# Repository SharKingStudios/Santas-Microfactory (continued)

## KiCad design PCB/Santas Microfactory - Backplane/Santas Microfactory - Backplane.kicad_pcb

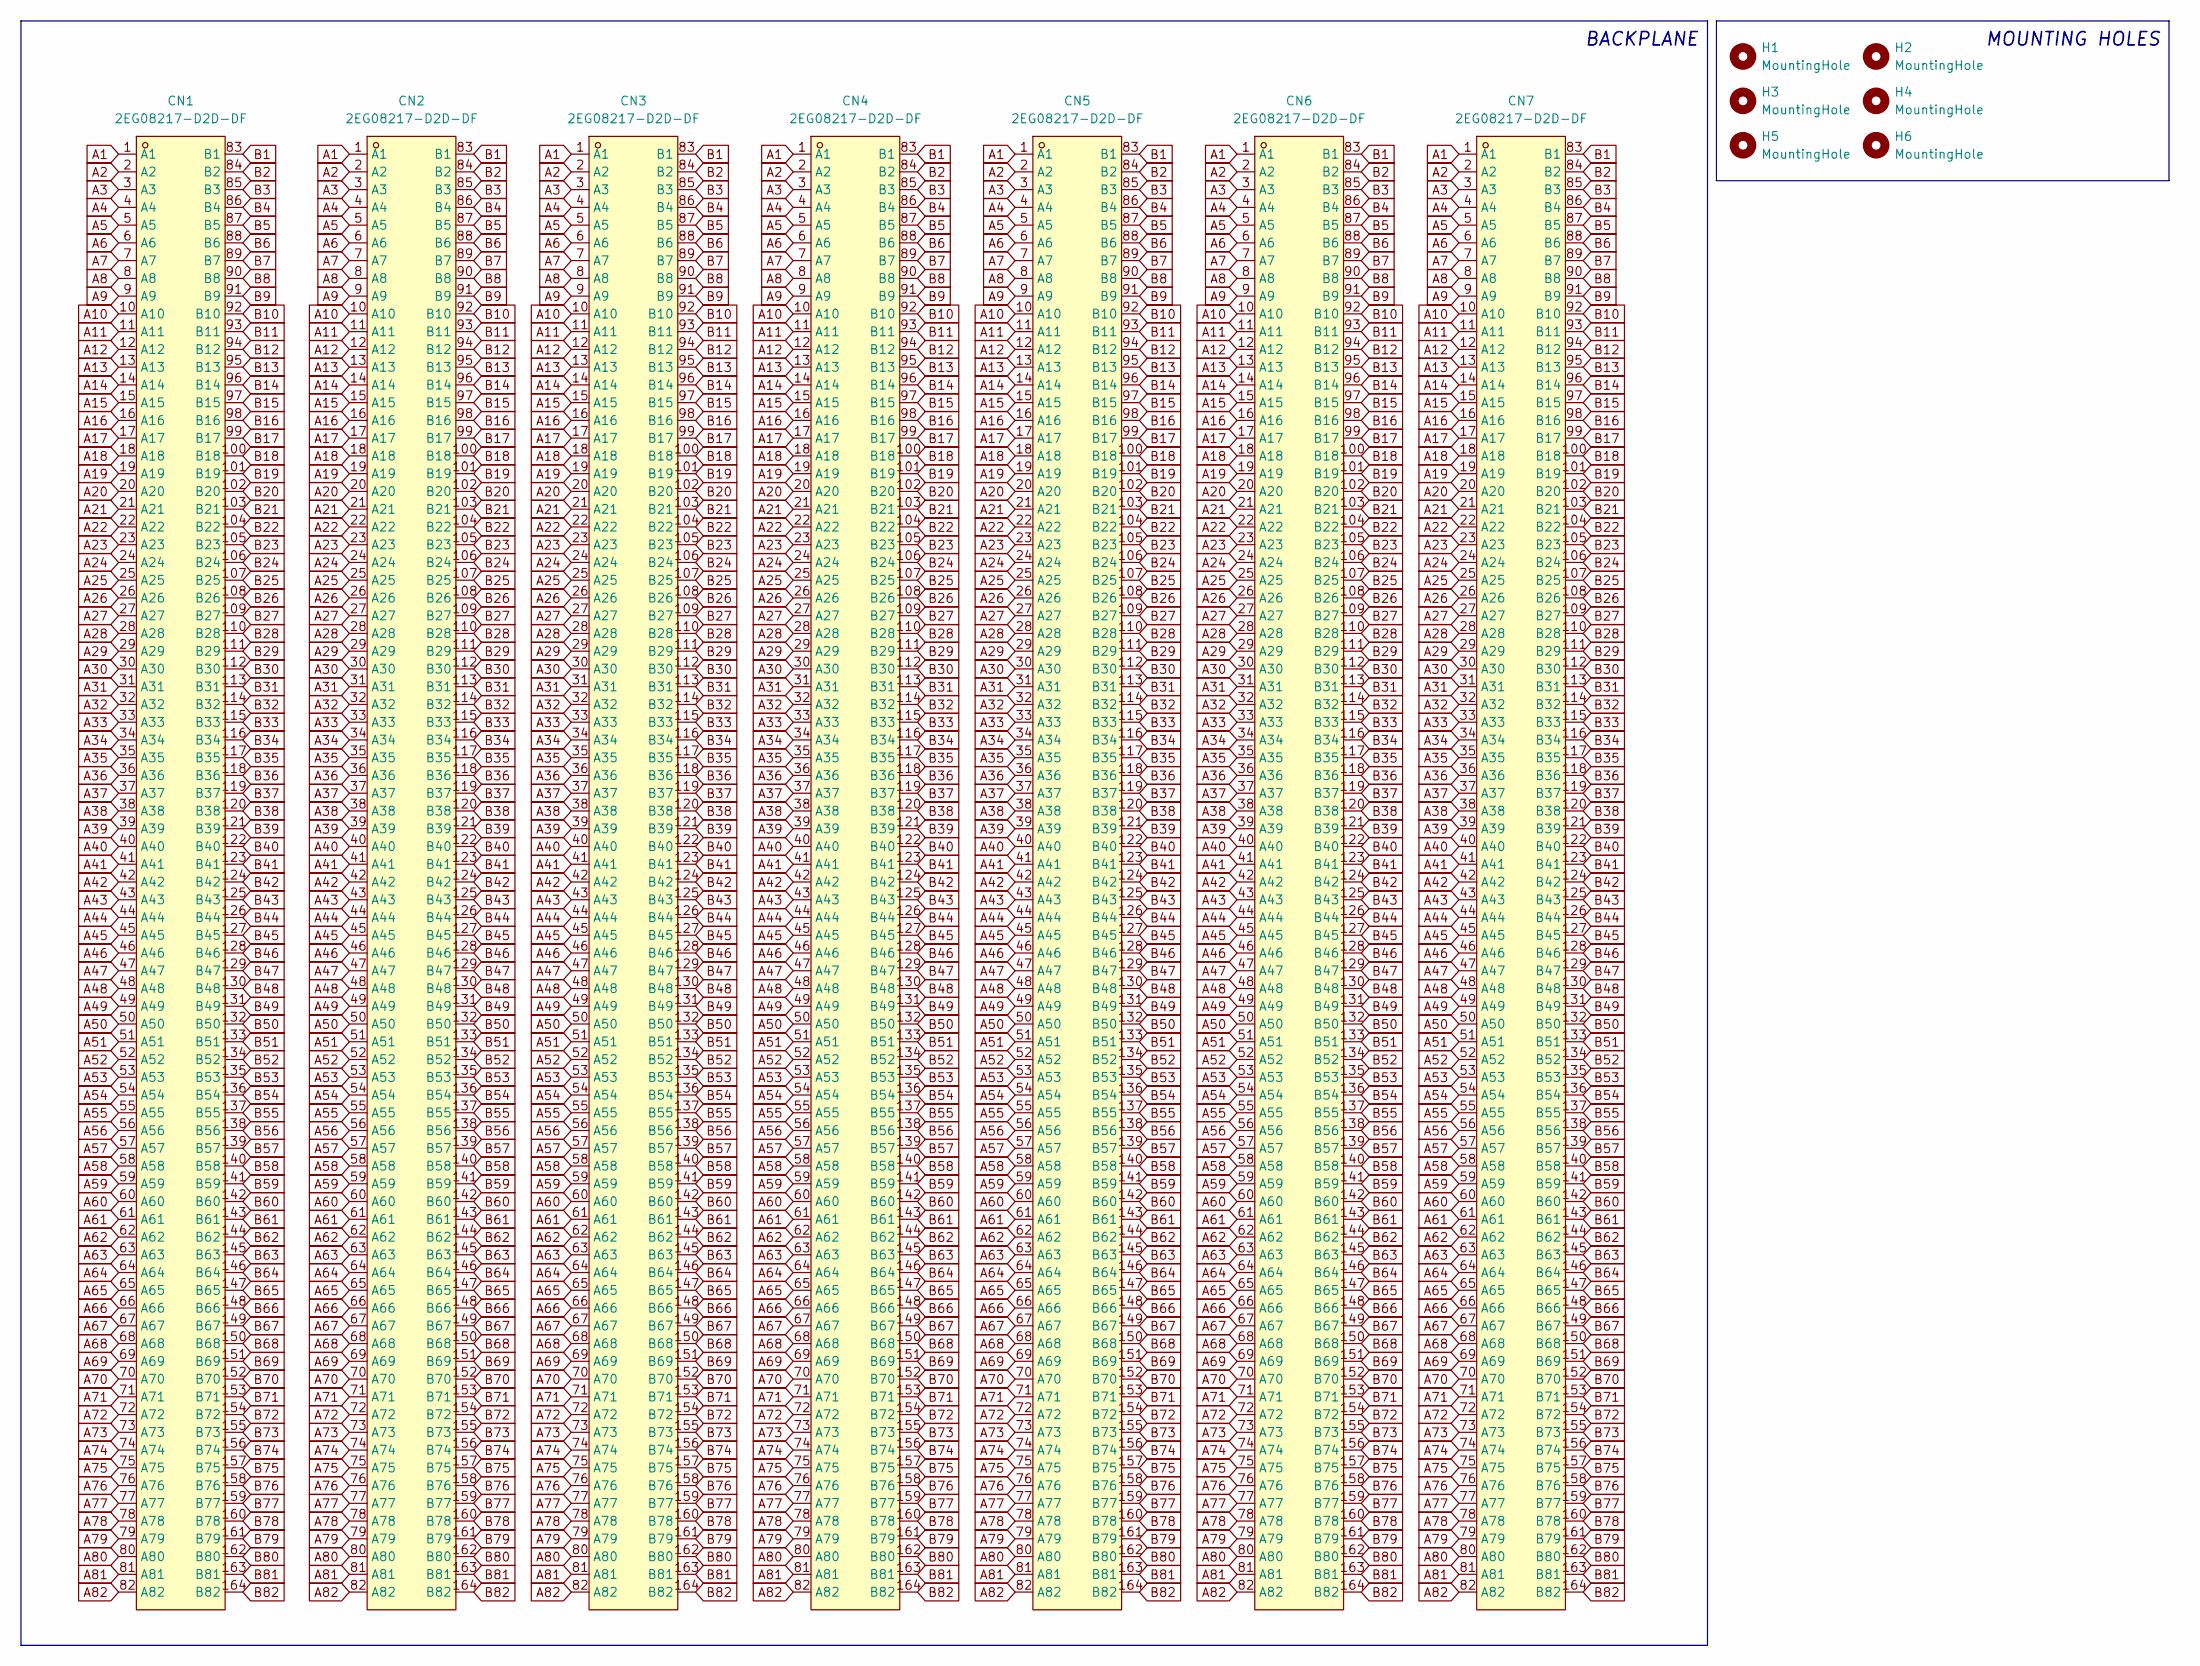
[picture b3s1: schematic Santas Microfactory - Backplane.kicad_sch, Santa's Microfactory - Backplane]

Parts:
CN1, CN2, CN3, CN4, CN5, CN6, CN7: 2EG08217-D2D-DF; CONN-TH_2EG08217-D2D-DF; LCSC Part C426228
H1, H2, H3, H4, H5, H6: MountingHole; MountingHole_3.2mm_M3_Pad_Via

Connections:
A1: CN1.1 (A1), CN2.1 (A1), CN3.1 (A1), CN4.1 (A1), CN5.1 (A1), CN6.1 (A1), CN7.1 (A1)
A2: CN1.2 (A2), CN2.2 (A2), CN3.2 (A2), CN4.2 (A2), CN5.2 (A2), CN6.2 (A2), CN7.2 (A2)
A3: CN1.3 (A3), CN2.3 (A3), CN3.3 (A3), CN4.3 (A3), CN5.3 (A3), CN6.3 (A3), CN7.3 (A3)
A4: CN1.4 (A4), CN2.4 (A4), CN3.4 (A4), CN4.4 (A4), CN5.4 (A4), CN6.4 (A4), CN7.4 (A4)
A5: CN1.5 (A5), CN2.5 (A5), CN3.5 (A5), CN4.5 (A5), CN5.5 (A5), CN6.5 (A5), CN7.5 (A5)
A6: CN1.6 (A6), CN2.6 (A6), CN3.6 (A6), CN4.6 (A6), CN5.6 (A6), CN6.6 (A6), CN7.6 (A6)
A7: CN1.7 (A7), CN2.7 (A7), CN3.7 (A7), CN4.7 (A7), CN5.7 (A7), CN6.7 (A7), CN7.7 (A7)
A8: CN1.8 (A8), CN2.8 (A8), CN3.8 (A8), CN4.8 (A8), CN5.8 (A8), CN6.8 (A8), CN7.8 (A8)
A9: CN1.9 (A9), CN2.9 (A9), CN3.9 (A9), CN4.9 (A9), CN5.9 (A9), CN6.9 (A9), CN7.9 (A9)
A10: CN1.10 (A10), CN2.10 (A10), CN3.10 (A10), CN4.10 (A10), CN5.10 (A10), CN6.10 (A10), CN7.10 (A10)
A11: CN1.11 (A11), CN2.11 (A11), CN3.11 (A11), CN4.11 (A11), CN5.11 (A11), CN6.11 (A11), CN7.11 (A11)
A12: CN1.12 (A12), CN2.12 (A12), CN3.12 (A12), CN4.12 (A12), CN5.12 (A12), CN6.12 (A12), CN7.12 (A12)
A13: CN1.13 (A13), CN2.13 (A13), CN3.13 (A13), CN4.13 (A13), CN5.13 (A13), CN6.13 (A13), CN7.13 (A13)
A14: CN1.14 (A14), CN2.14 (A14), CN3.14 (A14), CN4.14 (A14), CN5.14 (A14), CN6.14 (A14), CN7.14 (A14)
A15: CN1.15 (A15), CN2.15 (A15), CN3.15 (A15), CN4.15 (A15), CN5.15 (A15), CN6.15 (A15), CN7.15 (A15)
A16: CN1.16 (A16), CN2.16 (A16), CN3.16 (A16), CN4.16 (A16), CN5.16 (A16), CN6.16 (A16), CN7.16 (A16)
A17: CN1.17 (A17), CN2.17 (A17), CN3.17 (A17), CN4.17 (A17), CN5.17 (A17), CN6.17 (A17), CN7.17 (A17)
A18: CN1.18 (A18), CN2.18 (A18), CN3.18 (A18), CN4.18 (A18), CN5.18 (A18), CN6.18 (A18), CN7.18 (A18)
A19: CN1.19 (A19), CN2.19 (A19), CN3.19 (A19), CN4.19 (A19), CN5.19 (A19), CN6.19 (A19), CN7.19 (A19)
A20: CN1.20 (A20), CN2.20 (A20), CN3.20 (A20), CN4.20 (A20), CN5.20 (A20), CN6.20 (A20), CN7.20 (A20)
A21: CN1.21 (A21), CN2.21 (A21), CN3.21 (A21), CN4.21 (A21), CN5.21 (A21), CN6.21 (A21), CN7.21 (A21)
A22: CN1.22 (A22), CN2.22 (A22), CN3.22 (A22), CN4.22 (A22), CN5.22 (A22), CN6.22 (A22), CN7.22 (A22)
A23: CN1.23 (A23), CN2.23 (A23), CN3.23 (A23), CN4.23 (A23), CN5.23 (A23), CN6.23 (A23), CN7.23 (A23)
A24: CN1.24 (A24), CN2.24 (A24), CN3.24 (A24), CN4.24 (A24), CN5.24 (A24), CN6.24 (A24), CN7.24 (A24)
A25: CN1.25 (A25), CN2.25 (A25), CN3.25 (A25), CN4.25 (A25), CN5.25 (A25), CN6.25 (A25), CN7.25 (A25)
A26: CN1.26 (A26), CN2.26 (A26), CN3.26 (A26), CN4.26 (A26), CN5.26 (A26), CN6.26 (A26), CN7.26 (A26)
A27: CN1.27 (A27), CN2.27 (A27), CN3.27 (A27), CN4.27 (A27), CN5.27 (A27), CN6.27 (A27), CN7.27 (A27)
A28: CN1.28 (A28), CN2.28 (A28), CN3.28 (A28), CN4.28 (A28), CN5.28 (A28), CN6.28 (A28), CN7.28 (A28)
A29: CN1.29 (A29), CN2.29 (A29), CN3.29 (A29), CN4.29 (A29), CN5.29 (A29), CN6.29 (A29), CN7.29 (A29)
A30: CN1.30 (A30), CN2.30 (A30), CN3.30 (A30), CN4.30 (A30), CN5.30 (A30), CN6.30 (A30), CN7.30 (A30)
A31: CN1.31 (A31), CN2.31 (A31), CN3.31 (A31), CN4.31 (A31), CN5.31 (A31), CN6.31 (A31), CN7.31 (A31)
A32: CN1.32 (A32), CN2.32 (A32), CN3.32 (A32), CN4.32 (A32), CN5.32 (A32), CN6.32 (A32), CN7.32 (A32)
A33: CN1.33 (A33), CN2.33 (A33), CN3.33 (A33), CN4.33 (A33), CN5.33 (A33), CN6.33 (A33), CN7.33 (A33)
A34: CN1.34 (A34), CN2.34 (A34), CN3.34 (A34), CN4.34 (A34), CN5.34 (A34), CN6.34 (A34), CN7.34 (A34)
A35: CN1.35 (A35), CN2.35 (A35), CN3.35 (A35), CN4.35 (A35), CN5.35 (A35), CN6.35 (A35), CN7.35 (A35)
A36: CN1.36 (A36), CN2.36 (A36), CN3.36 (A36), CN4.36 (A36), CN5.36 (A36), CN6.36 (A36), CN7.36 (A36)
A37: CN1.37 (A37), CN2.37 (A37), CN3.37 (A37), CN4.37 (A37), CN5.37 (A37), CN6.37 (A37), CN7.37 (A37)
A38: CN1.38 (A38), CN2.38 (A38), CN3.38 (A38), CN4.38 (A38), CN5.38 (A38), CN6.38 (A38), CN7.38 (A38)
A39: CN1.39 (A39), CN2.39 (A39), CN3.39 (A39), CN4.39 (A39), CN5.39 (A39), CN6.39 (A39), CN7.39 (A39)
A40: CN1.40 (A40), CN2.40 (A40), CN3.40 (A40), CN4.40 (A40), CN5.40 (A40), CN6.40 (A40), CN7.40 (A40)
A41: CN1.41 (A41), CN2.41 (A41), CN3.41 (A41), CN4.41 (A41), CN5.41 (A41), CN6.41 (A41), CN7.41 (A41)
A42: CN1.42 (A42), CN2.42 (A42), CN3.42 (A42), CN4.42 (A42), CN5.42 (A42), CN6.42 (A42), CN7.42 (A42)
A43: CN1.43 (A43), CN2.43 (A43), CN3.43 (A43), CN4.43 (A43), CN5.43 (A43), CN6.43 (A43), CN7.43 (A43)
A44: CN1.44 (A44), CN2.44 (A44), CN3.44 (A44), CN4.44 (A44), CN5.44 (A44), CN6.44 (A44), CN7.44 (A44)
A45: CN1.45 (A45), CN2.45 (A45), CN3.45 (A45), CN4.45 (A45), CN5.45 (A45), CN6.45 (A45), CN7.45 (A45)
A46: CN1.46 (A46), CN2.46 (A46), CN3.46 (A46), CN4.46 (A46), CN5.46 (A46), CN6.46 (A46), CN7.46 (A46)
A47: CN1.47 (A47), CN2.47 (A47), CN3.47 (A47), CN4.47 (A47), CN5.47 (A47), CN6.47 (A47), CN7.47 (A47)
A48: CN1.48 (A48), CN2.48 (A48), CN3.48 (A48), CN4.48 (A48), CN5.48 (A48), CN6.48 (A48), CN7.48 (A48)
A49: CN1.49 (A49), CN2.49 (A49), CN3.49 (A49), CN4.49 (A49), CN5.49 (A49), CN6.49 (A49), CN7.49 (A49)
A50: CN1.50 (A50), CN2.50 (A50), CN3.50 (A50), CN4.50 (A50), CN5.50 (A50), CN6.50 (A50), CN7.50 (A50)
A51: CN1.51 (A51), CN2.51 (A51), CN3.51 (A51), CN4.51 (A51), CN5.51 (A51), CN6.51 (A51), CN7.51 (A51)
A52: CN1.52 (A52), CN2.52 (A52), CN3.52 (A52), CN4.52 (A52), CN5.52 (A52), CN6.52 (A52), CN7.52 (A52)
A53: CN1.53 (A53), CN2.53 (A53), CN3.53 (A53), CN4.53 (A53), CN5.53 (A53), CN6.53 (A53), CN7.53 (A53)
A54: CN1.54 (A54), CN2.54 (A54), CN3.54 (A54), CN4.54 (A54), CN5.54 (A54), CN6.54 (A54), CN7.54 (A54)
A55: CN1.55 (A55), CN2.55 (A55), CN3.55 (A55), CN4.55 (A55), CN5.55 (A55), CN6.55 (A55), CN7.55 (A55)
A56: CN1.56 (A56), CN2.56 (A56), CN3.56 (A56), CN4.56 (A56), CN5.56 (A56), CN6.56 (A56), CN7.56 (A56)
A57: CN1.57 (A57), CN2.57 (A57), CN3.57 (A57), CN4.57 (A57), CN5.57 (A57), CN6.57 (A57), CN7.57 (A57)
A58: CN1.58 (A58), CN2.58 (A58), CN3.58 (A58), CN4.58 (A58), CN5.58 (A58), CN6.58 (A58), CN7.58 (A58)
A59: CN1.59 (A59), CN2.59 (A59), CN3.59 (A59), CN4.59 (A59), CN5.59 (A59), CN6.59 (A59), CN7.59 (A59)
A60: CN1.60 (A60), CN2.60 (A60), CN3.60 (A60), CN4.60 (A60), CN5.60 (A60), CN6.60 (A60), CN7.60 (A60)
A61: CN1.61 (A61), CN2.61 (A61), CN3.61 (A61), CN4.61 (A61), CN5.61 (A61), CN6.61 (A61), CN7.61 (A61)
A62: CN1.62 (A62), CN2.62 (A62), CN3.62 (A62), CN4.62 (A62), CN5.62 (A62), CN6.62 (A62), CN7.62 (A62)
A63: CN1.63 (A63), CN2.63 (A63), CN3.63 (A63), CN4.63 (A63), CN5.63 (A63), CN6.63 (A63), CN7.63 (A63)
A64: CN1.64 (A64), CN2.64 (A64), CN3.64 (A64), CN4.64 (A64), CN5.64 (A64), CN6.64 (A64), CN7.64 (A64)
A65: CN1.65 (A65), CN2.65 (A65), CN3.65 (A65), CN4.65 (A65), CN5.65 (A65), CN6.65 (A65), CN7.65 (A65)
A66: CN1.66 (A66), CN2.66 (A66), CN3.66 (A66), CN4.66 (A66), CN5.66 (A66), CN6.66 (A66), CN7.66 (A66)
A67: CN1.67 (A67), CN2.67 (A67), CN3.67 (A67), CN4.67 (A67), CN5.67 (A67), CN6.67 (A67), CN7.67 (A67)
A68: CN1.68 (A68), CN2.68 (A68), CN3.68 (A68), CN4.68 (A68), CN5.68 (A68), CN6.68 (A68), CN7.68 (A68)
A69: CN1.69 (A69), CN2.69 (A69), CN3.69 (A69), CN4.69 (A69), CN5.69 (A69), CN6.69 (A69), CN7.69 (A69)
A70: CN1.70 (A70), CN2.70 (A70), CN3.70 (A70), CN4.70 (A70), CN5.70 (A70), CN6.70 (A70), CN7.70 (A70)
A71: CN1.71 (A71), CN2.71 (A71), CN3.71 (A71), CN4.71 (A71), CN5.71 (A71), CN6.71 (A71), CN7.71 (A71)
A72: CN1.72 (A72), CN2.72 (A72), CN3.72 (A72), CN4.72 (A72), CN5.72 (A72), CN6.72 (A72), CN7.72 (A72)
A73: CN1.73 (A73), CN2.73 (A73), CN3.73 (A73), CN4.73 (A73), CN5.73 (A73), CN6.73 (A73), CN7.73 (A73)
A74: CN1.74 (A74), CN2.74 (A74), CN3.74 (A74), CN4.74 (A74), CN5.74 (A74), CN6.74 (A74), CN7.74 (A74)
A75: CN1.75 (A75), CN2.75 (A75), CN3.75 (A75), CN4.75 (A75), CN5.75 (A75), CN6.75 (A75), CN7.75 (A75)
A76: CN1.76 (A76), CN2.76 (A76), CN3.76 (A76), CN4.76 (A76), CN5.76 (A76), CN6.76 (A76), CN7.76 (A76)
A77: CN1.77 (A77), CN2.77 (A77), CN3.77 (A77), CN4.77 (A77), CN5.77 (A77), CN6.77 (A77), CN7.77 (A77)
A78: CN1.78 (A78), CN2.78 (A78), CN3.78 (A78), CN4.78 (A78), CN5.78 (A78), CN6.78 (A78), CN7.78 (A78)
A79: CN1.79 (A79), CN2.79 (A79), CN3.79 (A79), CN4.79 (A79), CN5.79 (A79), CN6.79 (A79), CN7.79 (A79)
A80: CN1.80 (A80), CN2.80 (A80), CN3.80 (A80), CN4.80 (A80), CN5.80 (A80), CN6.80 (A80), CN7.80 (A80)
A81: CN1.81 (A81), CN2.81 (A81), CN3.81 (A81), CN4.81 (A81), CN5.81 (A81), CN6.81 (A81), CN7.81 (A81)
A82: CN1.82 (A82), CN2.82 (A82), CN3.82 (A82), CN4.82 (A82), CN5.82 (A82), CN6.82 (A82), CN7.82 (A82)
B1: CN1.83 (B1), CN2.83 (B1), CN3.83 (B1), CN4.83 (B1), CN5.83 (B1), CN6.83 (B1), CN7.83 (B1)
B2: CN1.84 (B2), CN2.84 (B2), CN3.84 (B2), CN4.84 (B2), CN5.84 (B2), CN6.84 (B2), CN7.84 (B2)
B3: CN1.85 (B3), CN2.85 (B3), CN3.85 (B3), CN4.85 (B3), CN5.85 (B3), CN6.85 (B3), CN7.85 (B3)
B4: CN1.86 (B4), CN2.86 (B4), CN3.86 (B4), CN4.86 (B4), CN5.86 (B4), CN6.86 (B4), CN7.86 (B4)
B5: CN1.87 (B5), CN2.87 (B5), CN3.87 (B5), CN4.87 (B5), CN5.87 (B5), CN6.87 (B5), CN7.87 (B5)
B6: CN1.88 (B6), CN2.88 (B6), CN3.88 (B6), CN4.88 (B6), CN5.88 (B6), CN6.88 (B6), CN7.88 (B6)
B7: CN1.89 (B7), CN2.89 (B7), CN3.89 (B7), CN4.89 (B7), CN5.89 (B7), CN6.89 (B7), CN7.89 (B7)
B8: CN1.90 (B8), CN2.90 (B8), CN3.90 (B8), CN4.90 (B8), CN5.90 (B8), CN6.90 (B8), CN7.90 (B8)
B9: CN1.91 (B9), CN2.91 (B9), CN3.91 (B9), CN4.91 (B9), CN5.91 (B9), CN6.91 (B9), CN7.91 (B9)
B10: CN1.92 (B10), CN2.92 (B10), CN3.92 (B10), CN4.92 (B10), CN5.92 (B10), CN6.92 (B10), CN7.92 (B10)
B11: CN1.93 (B11), CN2.93 (B11), CN3.93 (B11), CN4.93 (B11), CN5.93 (B11), CN6.93 (B11), CN7.93 (B11)
B12: CN1.94 (B12), CN2.94 (B12), CN3.94 (B12), CN4.94 (B12), CN5.94 (B12), CN6.94 (B12), CN7.94 (B12)
B13: CN1.95 (B13), CN2.95 (B13), CN3.95 (B13), CN4.95 (B13), CN5.95 (B13), CN6.95 (B13), CN7.95 (B13)
B14: CN1.96 (B14), CN2.96 (B14), CN3.96 (B14), CN4.96 (B14), CN5.96 (B14), CN6.96 (B14), CN7.96 (B14)
B15: CN1.97 (B15), CN2.97 (B15), CN3.97 (B15), CN4.97 (B15), CN5.97 (B15), CN6.97 (B15), CN7.97 (B15)
B16: CN1.98 (B16), CN2.98 (B16), CN3.98 (B16), CN4.98 (B16), CN5.98 (B16), CN6.98 (B16), CN7.98 (B16)
B17: CN1.99 (B17), CN2.99 (B17), CN3.99 (B17), CN4.99 (B17), CN5.99 (B17), CN6.99 (B17), CN7.99 (B17)
B18: CN1.100 (B18), CN2.100 (B18), CN3.100 (B18), CN4.100 (B18), CN5.100 (B18), CN6.100 (B18), CN7.100 (B18)
B19: CN1.101 (B19), CN2.101 (B19), CN3.101 (B19), CN4.101 (B19), CN5.101 (B19), CN6.101 (B19), CN7.101 (B19)
B20: CN1.102 (B20), CN2.102 (B20), CN3.102 (B20), CN4.102 (B20), CN5.102 (B20), CN6.102 (B20), CN7.102 (B20)
B21: CN1.103 (B21), CN2.103 (B21), CN3.103 (B21), CN4.103 (B21), CN5.103 (B21), CN6.103 (B21), CN7.103 (B21)
B22: CN1.104 (B22), CN2.104 (B22), CN3.104 (B22), CN4.104 (B22), CN5.104 (B22), CN6.104 (B22), CN7.104 (B22)
B23: CN1.105 (B23), CN2.105 (B23), CN3.105 (B23), CN4.105 (B23), CN5.105 (B23), CN6.105 (B23), CN7.105 (B23)
B24: CN1.106 (B24), CN2.106 (B24), CN3.106 (B24), CN4.106 (B24), CN5.106 (B24), CN6.106 (B24), CN7.106 (B24)
B25: CN1.107 (B25), CN2.107 (B25), CN3.107 (B25), CN4.107 (B25), CN5.107 (B25), CN6.107 (B25), CN7.107 (B25)
B26: CN1.108 (B26), CN2.108 (B26), CN3.108 (B26), CN4.108 (B26), CN5.108 (B26), CN6.108 (B26), CN7.108 (B26)
B27: CN1.109 (B27), CN2.109 (B27), CN3.109 (B27), CN4.109 (B27), CN5.109 (B27), CN6.109 (B27), CN7.109 (B27)
B28: CN1.110 (B28), CN2.110 (B28), CN3.110 (B28), CN4.110 (B28), CN5.110 (B28), CN6.110 (B28), CN7.110 (B28)
B29: CN1.111 (B29), CN2.111 (B29), CN3.111 (B29), CN4.111 (B29), CN5.111 (B29), CN6.111 (B29), CN7.111 (B29)
B30: CN1.112 (B30), CN2.112 (B30), CN3.112 (B30), CN4.112 (B30), CN5.112 (B30), CN6.112 (B30), CN7.112 (B30)
B31: CN1.113 (B31), CN2.113 (B31), CN3.113 (B31), CN4.113 (B31), CN5.113 (B31), CN6.113 (B31), CN7.113 (B31)
B32: CN1.114 (B32), CN2.114 (B32), CN3.114 (B32), CN4.114 (B32), CN5.114 (B32), CN6.114 (B32), CN7.114 (B32)
B33: CN1.115 (B33), CN2.115 (B33), CN3.115 (B33), CN4.115 (B33), CN5.115 (B33), CN6.115 (B33), CN7.115 (B33)
B34: CN1.116 (B34), CN2.116 (B34), CN3.116 (B34), CN4.116 (B34), CN5.116 (B34), CN6.116 (B34), CN7.116 (B34)
B35: CN1.117 (B35), CN2.117 (B35), CN3.117 (B35), CN4.117 (B35), CN5.117 (B35), CN6.117 (B35), CN7.117 (B35)
B36: CN1.118 (B36), CN2.118 (B36), CN3.118 (B36), CN4.118 (B36), CN5.118 (B36), CN6.118 (B36), CN7.118 (B36)
B37: CN1.119 (B37), CN2.119 (B37), CN3.119 (B37), CN4.119 (B37), CN5.119 (B37), CN6.119 (B37), CN7.119 (B37)
B38: CN1.120 (B38), CN2.120 (B38), CN3.120 (B38), CN4.120 (B38), CN5.120 (B38), CN6.120 (B38), CN7.120 (B38)
B39: CN1.121 (B39), CN2.121 (B39), CN3.121 (B39), CN4.121 (B39), CN5.121 (B39), CN6.121 (B39), CN7.121 (B39)
B40: CN1.122 (B40), CN2.122 (B40), CN3.122 (B40), CN4.122 (B40), CN5.122 (B40), CN6.122 (B40), CN7.122 (B40)
B41: CN1.123 (B41), CN2.123 (B41), CN3.123 (B41), CN4.123 (B41), CN5.123 (B41), CN6.123 (B41), CN7.123 (B41)
B42: CN1.124 (B42), CN2.124 (B42), CN3.124 (B42), CN4.124 (B42), CN5.124 (B42), CN6.124 (B42), CN7.124 (B42)
B43: CN1.125 (B43), CN2.125 (B43), CN3.125 (B43), CN4.125 (B43), CN5.125 (B43), CN6.125 (B43), CN7.125 (B43)
B44: CN1.126 (B44), CN2.126 (B44), CN3.126 (B44), CN4.126 (B44), CN5.126 (B44), CN6.126 (B44), CN7.126 (B44)
B45: CN1.127 (B45), CN2.127 (B45), CN3.127 (B45), CN4.127 (B45), CN5.127 (B45), CN6.127 (B45), CN7.127 (B45)
B46: CN1.128 (B46), CN2.128 (B46), CN3.128 (B46), CN4.128 (B46), CN5.128 (B46), CN6.128 (B46), CN7.128 (B46)
B47: CN1.129 (B47), CN2.129 (B47), CN3.129 (B47), CN4.129 (B47), CN5.129 (B47), CN6.129 (B47), CN7.129 (B47)
B48: CN1.130 (B48), CN2.130 (B48), CN3.130 (B48), CN4.130 (B48), CN5.130 (B48), CN6.130 (B48), CN7.130 (B48)
B49: CN1.131 (B49), CN2.131 (B49), CN3.131 (B49), CN4.131 (B49), CN5.131 (B49), CN6.131 (B49), CN7.131 (B49)
B50: CN1.132 (B50), CN2.132 (B50), CN3.132 (B50), CN4.132 (B50), CN5.132 (B50), CN6.132 (B50), CN7.132 (B50)
B51: CN1.133 (B51), CN2.133 (B51), CN3.133 (B51), CN4.133 (B51), CN5.133 (B51), CN6.133 (B51), CN7.133 (B51)
B52: CN1.134 (B52), CN2.134 (B52), CN3.134 (B52), CN4.134 (B52), CN5.134 (B52), CN6.134 (B52), CN7.134 (B52)
B53: CN1.135 (B53), CN2.135 (B53), CN3.135 (B53), CN4.135 (B53), CN5.135 (B53), CN6.135 (B53), CN7.135 (B53)
B54: CN1.136 (B54), CN2.136 (B54), CN3.136 (B54), CN4.136 (B54), CN5.136 (B54), CN6.136 (B54), CN7.136 (B54)
B55: CN1.137 (B55), CN2.137 (B55), CN3.137 (B55), CN4.137 (B55), CN5.137 (B55), CN6.137 (B55), CN7.137 (B55)
B56: CN1.138 (B56), CN2.138 (B56), CN3.138 (B56), CN4.138 (B56), CN5.138 (B56), CN6.138 (B56), CN7.138 (B56)
B57: CN1.139 (B57), CN2.139 (B57), CN3.139 (B57), CN4.139 (B57), CN5.139 (B57), CN6.139 (B57), CN7.139 (B57)
B58: CN1.140 (B58), CN2.140 (B58), CN3.140 (B58), CN4.140 (B58), CN5.140 (B58), CN6.140 (B58), CN7.140 (B58)
B59: CN1.141 (B59), CN2.141 (B59), CN3.141 (B59), CN4.141 (B59), CN5.141 (B59), CN6.141 (B59), CN7.141 (B59)
B60: CN1.142 (B60), CN2.142 (B60), CN3.142 (B60), CN4.142 (B60), CN5.142 (B60), CN6.142 (B60), CN7.142 (B60)
B61: CN1.143 (B61), CN2.143 (B61), CN3.143 (B61), CN4.143 (B61), CN5.143 (B61), CN6.143 (B61), CN7.143 (B61)
B62: CN1.144 (B62), CN2.144 (B62), CN3.144 (B62), CN4.144 (B62), CN5.144 (B62), CN6.144 (B62), CN7.144 (B62)
B63: CN1.145 (B63), CN2.145 (B63), CN3.145 (B63), CN4.145 (B63), CN5.145 (B63), CN6.145 (B63), CN7.145 (B63)
B64: CN1.146 (B64), CN2.146 (B64), CN3.146 (B64), CN4.146 (B64), CN5.146 (B64), CN6.146 (B64), CN7.146 (B64)
B65: CN1.147 (B65), CN2.147 (B65), CN3.147 (B65), CN4.147 (B65), CN5.147 (B65), CN6.147 (B65), CN7.147 (B65)
B66: CN1.148 (B66), CN2.148 (B66), CN3.148 (B66), CN4.148 (B66), CN5.148 (B66), CN6.148 (B66), CN7.148 (B66)
B67: CN1.149 (B67), CN2.149 (B67), CN3.149 (B67), CN4.149 (B67), CN5.149 (B67), CN6.149 (B67), CN7.149 (B67)
B68: CN1.150 (B68), CN2.150 (B68), CN3.150 (B68), CN4.150 (B68), CN5.150 (B68), CN6.150 (B68), CN7.150 (B68)
B69: CN1.151 (B69), CN2.151 (B69), CN3.151 (B69), CN4.151 (B69), CN5.151 (B69), CN6.151 (B69), CN7.151 (B69)
B70: CN1.152 (B70), CN2.152 (B70), CN3.152 (B70), CN4.152 (B70), CN5.152 (B70), CN6.152 (B70), CN7.152 (B70)
B71: CN1.153 (B71), CN2.153 (B71), CN3.153 (B71), CN4.153 (B71), CN5.153 (B71), CN6.153 (B71), CN7.153 (B71)
B72: CN1.154 (B72), CN2.154 (B72), CN3.154 (B72), CN4.154 (B72), CN5.154 (B72), CN6.154 (B72), CN7.154 (B72)
B73: CN1.155 (B73), CN2.155 (B73), CN3.155 (B73), CN4.155 (B73), CN5.155 (B73), CN6.155 (B73), CN7.155 (B73)
B74: CN1.156 (B74), CN2.156 (B74), CN3.156 (B74), CN4.156 (B74), CN5.156 (B74), CN6.156 (B74), CN7.156 (B74)
B75: CN1.157 (B75), CN2.157 (B75), CN3.157 (B75), CN4.157 (B75), CN5.157 (B75), CN6.157 (B75), CN7.157 (B75)
B76: CN1.158 (B76), CN2.158 (B76), CN3.158 (B76), CN4.158 (B76), CN5.158 (B76), CN6.158 (B76), CN7.158 (B76)
B77: CN1.159 (B77), CN2.159 (B77), CN3.159 (B77), CN4.159 (B77), CN5.159 (B77), CN6.159 (B77), CN7.159 (B77)
B78: CN1.160 (B78), CN2.160 (B78), CN3.160 (B78), CN4.160 (B78), CN5.160 (B78), CN6.160 (B78), CN7.160 (B78)
B79: CN1.161 (B79), CN2.161 (B79), CN3.161 (B79), CN4.161 (B79), CN5.161 (B79), CN6.161 (B79), CN7.161 (B79)
B80: CN1.162 (B80), CN2.162 (B80), CN3.162 (B80), CN4.162 (B80), CN5.162 (B80), CN6.162 (B80), CN7.162 (B80)
B81: CN1.163 (B81), CN2.163 (B81), CN3.163 (B81), CN4.163 (B81), CN5.163 (B81), CN6.163 (B81), CN7.163 (B81)
B82: CN1.164 (B82), CN2.164 (B82), CN3.164 (B82), CN4.164 (B82), CN5.164 (B82), CN6.164 (B82), CN7.164 (B82)

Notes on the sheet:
MOUNTING HOLES
BACKPLANE

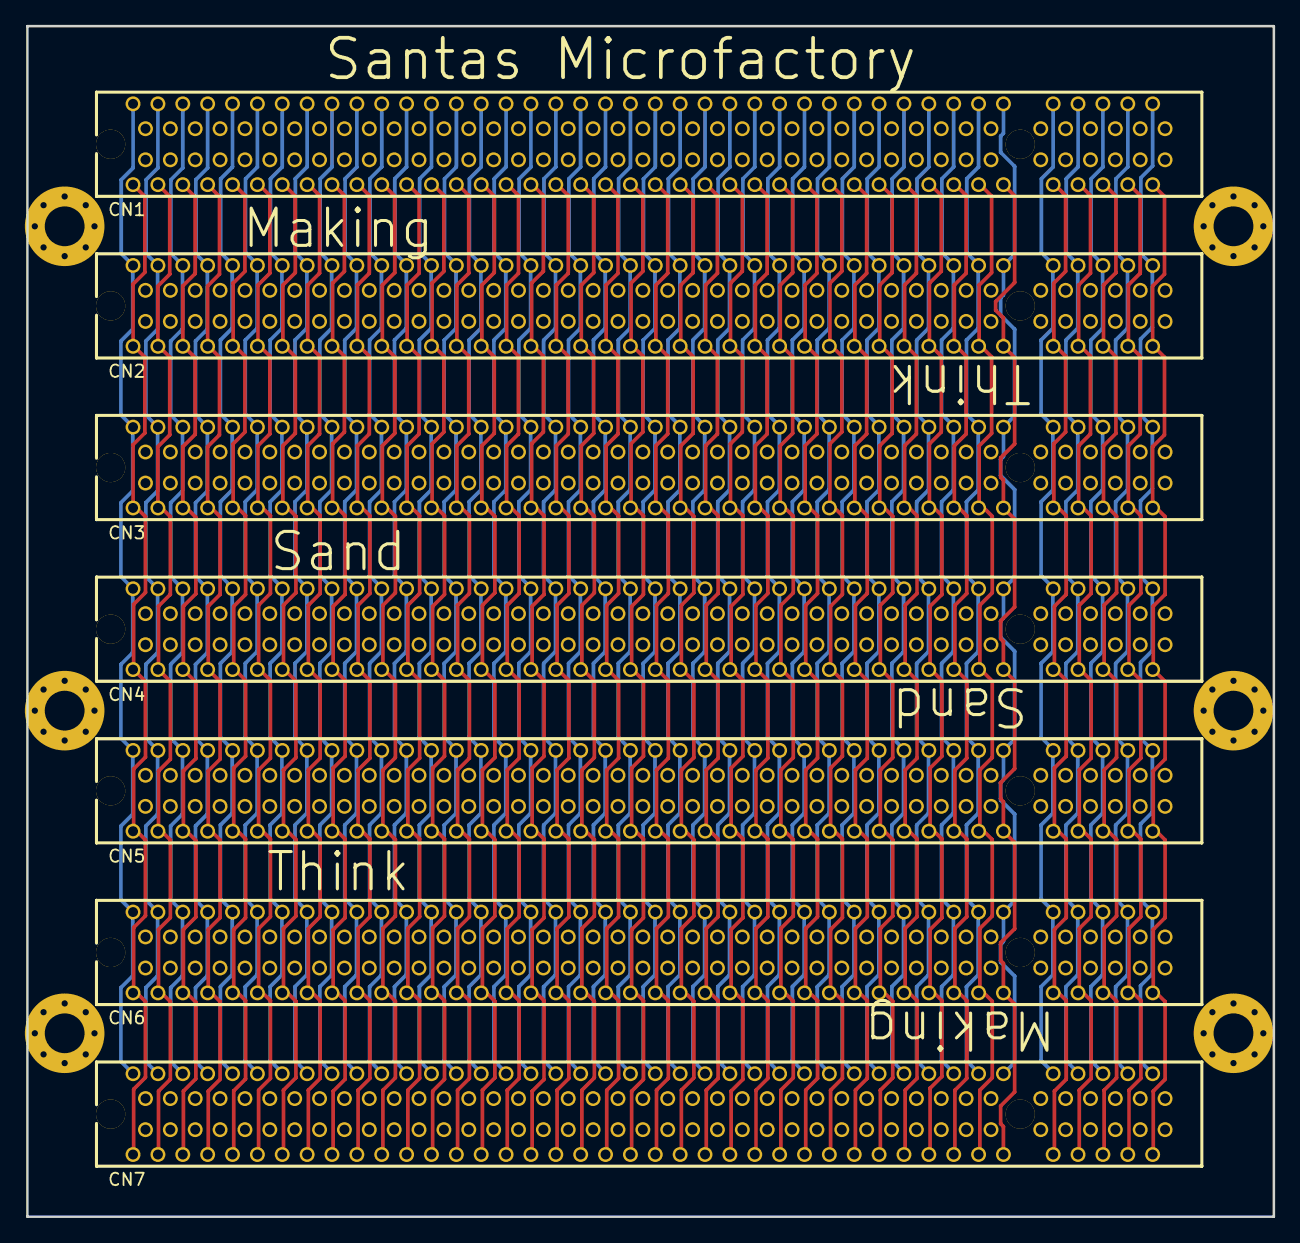
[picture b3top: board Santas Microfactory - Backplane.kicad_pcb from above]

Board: 4 copper layers, 100.2 x 95.8 mm, 13 parts (0 on the bottom side), 164 nets.

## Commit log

2026-01-03 Conveyor and Chute implementation
2026-01-04 Clock and game "RNG"
2026-01-05 The work keeps multiplying
2026-01-05 More work
2026-01-05 Scoring and Health Board Layout Done
2026-01-24 Finished Backplane
2026-01-25 Chutes Done + Main Conveyor Layout
2026-01-26 Main Conveyor Done
2026-01-30 Update Input Output Board
2026-04-05 Input Output Board Finished
2026-04-06 PCB 3D models
2026-05-13 All silkscreen additions + Gerbers and CAD files
    Silkscreen and Gerbers are done, but I plan on using the CAD to create additional renders.
2026-05-13 Updated PCB dates
2026-05-13 Updated Chutes PCB 1
